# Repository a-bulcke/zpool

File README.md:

# zpool V2
Carte Zigbbe de gestion de piscine avec mesure pH, Orp, température et pression

### ATTENTION ERREUR R26=0 ohm

**Les nouveautés :** 

    Filtre sur l'alimentation USB du Xiao

    Régulation LDO coté capteurs pour enlever les bruits provenant du Xiao et de l'ADM3260.

    Alimentation AOP et ADS1115 en 4.7V

    Utilisation d'une référence de tension 2.35V (4.7/2) au lieu des ponts diviseurs non bufferisés

    Gain Orp passe de 2.32 à 2

    Guard ring pour éviter les courants de fuite au niveau des sondes (dont l'impédance est très élevé ce qui peut expliquer l'éventuelle dérive sur la v1.0)

    Connecteur I2C en 3.3V pour écran Oled ou autre

**Sources :** 

https://github.com/Loic74650/pH_Orp_Board

https://www.360customs.de/fr/2019/12/orp-redox-ph-elektrometer-shield-fuer-wemos-d1-mini-mit-lmp7721-ads1115-adm3260/

https://www.ti.com/lit/ds/symlink/lmp7721.pdf?ts=1769807145680&ref_url=https%253A%252F%252Fwww.ti.com%252Fproduct%252FLMP7721

## Xiao ESP32C6
Utilisation d'un ESP32C6 pour en faire un routeur Zigbee.

Fonctionne avec Zigbee2Mqtt sous Home Assistant.

La carte mesure le pH, l’ Orp, la température et la pression.

La gestion des pompes est assurée par des prises Zigbee c’est plus simple que d’ajouter des relais à la carte.

# Branchements #
## température et pression ##

## pH et Orp ##

# Zigbee2Mqtt #
Dans Zigbee2mqtt sous Home Assistant, laller dans le menu `Paramètres` puis `console de developpement - convertisseurs externes` :

Créer un nouveau convertisseur (de nom ZPool.js) et coller le contenu de [ZPool.js](https://github.com/a-bulcke/zpool/blob/main/zigbee2mqtt/ZPool.js)

Redémarrer Zigbee2mqtt puis autoriser l'association.

# Mise à jour

## Programmation - Mise à jour

Dans Arduino IDE

Dans File - Preferences... ajouter :

```https://espressif.github.io/arduino-esp32/package_esp32_index.json```

Choisir une carte XIAO_ESP32C6 :

Dans Tools choisir Partition scheme: "Zigbee ZCZR 4MB with spiffs" et Zigbee Mode: "ZCZR (coordinator/router)"

Et copier coller le code dans Arduino IDE :

Mettre ```Erase All Flash before sketch Upload : Disabled``` pour conserver l'appairage zigbee

Installer les bibliothèques : 
Chercher et installer : 
```
#include "OneWireESP32.h" //esp32-ds18b20 par junkfix
#include <ADS1X15.h> //ADS1X15 par Rob Tillaart
#include "RunningAverage.h" // RunningAverage par Rob Tillaart
```

Puis Upload :

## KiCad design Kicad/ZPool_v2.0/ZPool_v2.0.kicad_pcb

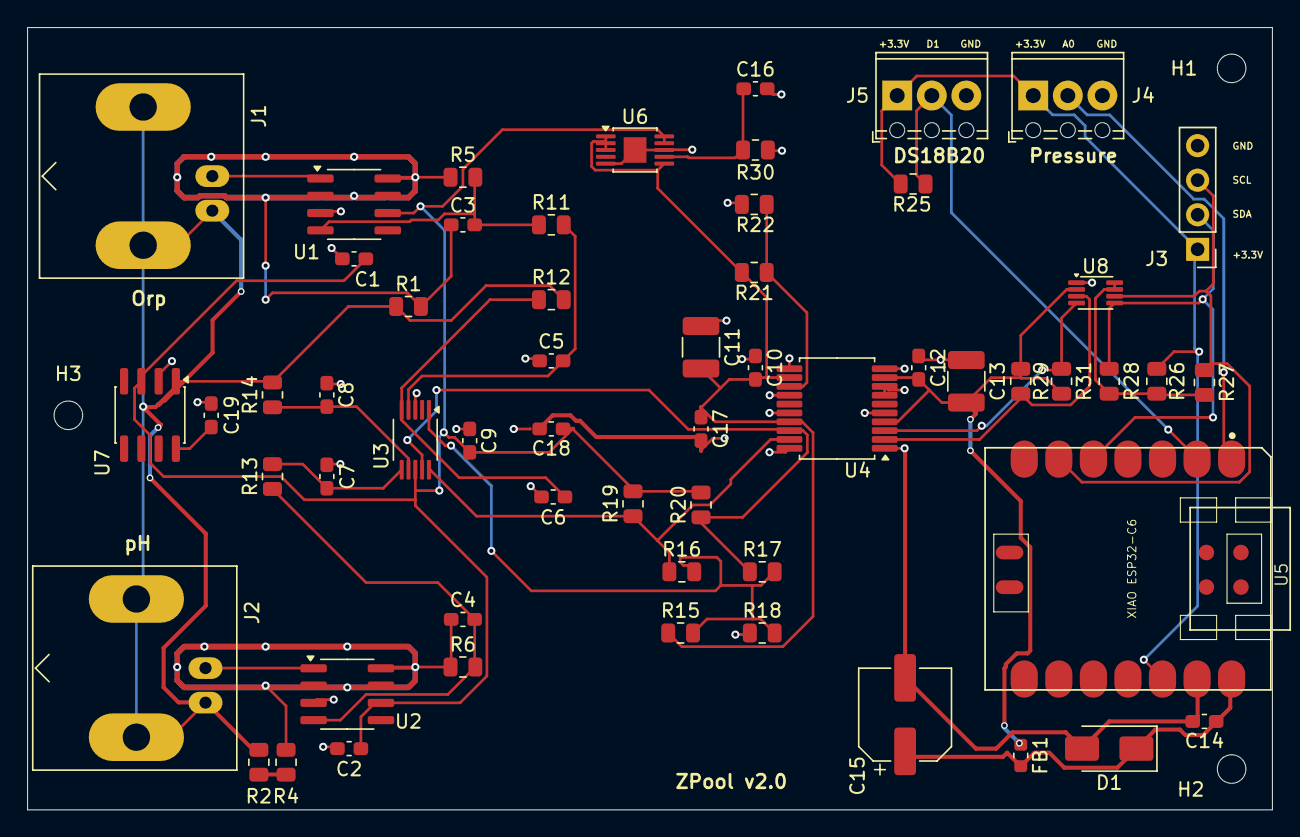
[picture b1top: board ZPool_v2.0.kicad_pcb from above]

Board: 2 copper layers, 91.5 x 57.5 mm, 61 parts (0 on the bottom side), 30 nets.

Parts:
C1, C2, C3, C4, C9, C10, C12: 100nF; C_0603_1608Metric_Pad1.08x0.95mm_HandSolder
C5, C6, C7, C8: 1uF; C_0603_1608Metric_Pad1.08x0.95mm_HandSolder
C11, C13: 10uF; C_1210_3225Metric_Pad1.33x2.70mm_HandSolder
C14: 100n; C_0603_1608Metric_Pad1.08x0.95mm_HandSolder
C15: 470u; CP_Elec_6.3x5.7
C16: 10nF; C_0603_1608Metric_Pad1.08x0.95mm_HandSolder
C17, C18: 4.7uF; C_0603_1608Metric_Pad1.08x0.95mm_HandSolder
C19: 1nF; C_0603_1608Metric_Pad1.08x0.95mm_HandSolder
D1: SMAJ5.0A; D_SMA
FB1: FerriteBead; L_0603_1608Metric
H1, H2, H3: MountingHole; MountingHole_2.1mm
J1, J2: Conn_Coaxial; BNC_Amphenol_B6252HB-NPP3G-50_Horizontal
J3: Conn_01x04_Male; PinHeader_1x04_P2.54mm_Vertical
J4: Conn_Pression; TerminalBlock_Phoenix_MPT-0,5-3-2.54_1x03_P2.54mm_Horizontal
J5: Conn_DS18B20; TerminalBlock_Phoenix_MPT-0,5-3-2.54_1x03_P2.54mm_Horizontal
R1, R5: 150K; R_0805_2012Metric
R2: 100K; R_0805_2012Metric
R4: 51K; R_0805_2012Metric
R6: 1M; R_0805_2012Metric
R11, R12, R13, R14: 10K; R_0805_2012Metric
R15, R16, R17, R18: 0; R_0805_2012Metric
R19, R20, R25, R27, R28, R29, R31: 4K7; R_0805_2012Metric
R21: R30.9K; R_0805_2012Metric
R22: R10K; R_0805_2012Metric
R26: 200K; R_0805_2012Metric
R30: 47K; R_0805_2012Metric
U1, U2: LMP7721MA/NOPB; SOIC-8_3.9x4.9mm_P1.27mm
U3: ADS1115IDGS; VSSOP-10_3x3mm_P0.5mm
U4: ADM3260; SSOP-20_5.3x7.2mm_P0.65mm
U5: XIAO ESP32-C6; Seeeduino XIAO-MOUDLE14P-2.54-21X17.8MM
U6: LT3042xMSE; MSOP-10-1EP_3x3mm_P0.5mm_EP1.68x1.88mm
U7: TLE2426xD; SOIC-8_3.9x4.9mm_P1.27mm
U8: PCA9306; VSSOP-8_2.3x2mm_P0.5mm

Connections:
+2.35V Iso: J1.2 (Ext), J2.2 (Ext), R1.1, R2.1, R12.2, R14.2, U7.1 (OUT)
+3.3V: J3.1, J4.1, J5.1, R25.1, R26.2, U5.12 (3V3)
+4.7V Iso: C1.2, C2.2, C9.2, C18.1, R19.2, R20.2, U1.6, U2.6, U3.8 (VDD), U6.9 (OUTS), U6.10 (OUT), U7.3 (IN)
+5V: C12.2, C13.2, FB1.1, R29.2, R31.2, U4.4 (VDDP), U4.9 (VIN), U8.2 (VREF1)
+5V Iso: C10.2, C11.2, C17.1, R15.1, R21.1, U4.12 (VISO), U4.17 (VDDISO), U6.1 (IN), U6.2 (IN), U6.3 (EN/UV), U6.6 (PGFB)
+5V_XIAO: C14.1, C15.1, D1.1 (A1), FB1.2, U5.14 (5V)
A0: J4.2, U5.1 (PA02_A0_D0)
D1: J5.2, R25.2, U5.2 (PA4_A1_D1)
GND: C12.1, C13.1, C14.2, C15.2, D1.2 (A2), J3.4, J4.3, J5.3, U4.1 (GNDP@1), U4.5 (GNDP@2), U4.7 (GNDP@2), U4.8 (PDIS), U4.10 (GNDP@2), U5.13 (GND), U8.1 (GND)
GND Iso: C1.1, C2.1, C5.1, C6.1, C7.1, C8.1, C9.1, C10.1, C11.1, C16.2, C17.2, C18.2, C19.2, R18.1, R22.1, R30.1, U1.3, U2.3, U3.3 (GND), U4.11 (GNDISO@2), U4.14 (GNDISO@2), U4.16 (GNDISO@2), U4.20 (GNDISO@1), U6.5 (ILIM), U6.8 (GND), U6.11 (GND), U7.2 (COMMON)
unnamed: C3.2, R5.2, R11.1, U1.4
unnamed: C4.2, R6.2, R13.1, U2.4
unnamed: J1.1 (In), U1.1
unnamed: J2.1 (In), U2.1
unnamed: R2.2, R4.1
unnamed: R15.2, R16.2, R17.2, R18.2, U3.1 (ADDR)
unnamed: C5.2, R11.2, U3.4 (AIN0)
unnamed: C6.2, R12.1, U3.5 (AIN1)
unnamed: C7.2, R13.2, U3.6 (AIN2)
unnamed: C8.2, R14.1, U3.7 (AIN3)
unnamed: R16.1, R19.1, U3.10 (SCL), U4.19 (SCL1)
unnamed: R17.1, R20.1, U3.9 (SDA), U4.18 (SDA1)
unnamed: R21.2, R22.2, U4.13 (VSEL)
unnamed: C16.1, R30.2, U6.7 (SET)
unnamed: C19.1, U7.8 (NOISE_REDUCTION)
unnamed: R26.1, R27.2, R28.2, U8.7 (VREF2), U8.8 (EN)
SCL: R29.1, U4.2 (SCL2), U8.3 (SCL1)
SCL3.3: J3.3, R27.1, U5.6 (PA9_A5_D5_SCL), U8.6 (SCL2)
SDA: R31.1, U4.3 (SDA2), U8.4 (SDA1)
SDA3.3: J3.2, R28.1, U5.5 (PA8_A4_D4_SDA), U8.5 (SDA2)

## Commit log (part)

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2026-01-30 v1.0
2026-01-30 Update README with sources and images
    Added source links and images to README.
2026-01-30 Add image of Boitier to README
2026-01-31 Add temperature and pressure sensor images to README
2026-01-31 Enhance README for ESP32C6 Zigbee router
    Updated the description of the ESP32C6 usage and added functionality details. Included images with specified widths.
2026-02-05 Add carte_xiao image to README
    Added image of carte_xiao to the README.
2026-02-05 Add Zigbee module image to README
    Added an image of the Zigbee module to the README.
2026-02-06 Add additional image to README
2026-02-06 Replace zpoolv1.png with zpoolv1.jpg in README
2026-02-14 Update README with Arduino IDE configuration details
    Added Arduino IDE setup instructions for XIAO_ESP32C6.
2026-02-14 Update README with new connection sections
    Added sections for temperature, pressure, pH, and Zigbee2Mqtt.
2026-02-14 Update README with converter creation instructions
    Updated instructions for creating a new converter in Zigbee2mqtt, including a link to the ZigbeePoolSensorsCalib.js file.
2026-02-14 Update README with additional instructions for Zigbee2mqtt
2026-03-18 Fix image link format for DS18B20 sensor
    Updated the image link format for temperature sensor.
2026-03-18 Fix image link for DS18B20 temperature sensor
    Updated the image link for the DS18B20 temperature sensor in the README.
2026-03-18 Change temperature sensor image URL
    Updated image link for temperature sensor in README.
2026-03-18 Fix image URLs in README
    Updated image URLs for temperature and pressure sensors.
2026-03-28 Change pH reporting change threshold to 0.05
2026-03-28 Add Zigbee temperature and pressure sensor code
2026-03-29 Update version to 1.11 and add external antenna config
2026-03-29 Add initial configuration for pool sensors
2026-03-29 Configure WIFI_ENABLE pin for external antenna
2026-03-29 Update README with sensor images and links
    Added images and links for temperature and pressure sensors.
2026-03-31 Update README with Arduino IDE programming instructions
    Added instructions for programming with Arduino IDE and configuring Zigbee settings.
2026-03-31 Improve code snippet formatting in README
    Updated formatting for URLs and code snippets in the README.
2026-03-31 Revise programming instructions and add images
    Updated programming section with new instructions and images.
2026-03-31 Update project version from V1.0 to V1
2026-04-11 Update version to 1.12 and adjust ORP reading
2026-05-24 Fix comment formatting for pH calculation
2026-05-30 1.3.3 pre release
    Version préliminaire avec choix des solutions d'étalonnage, 3 points d'étalonnage pour le pH, OTA, et filtre de Kalman.
2026-05-30 Update README with image and sources
    Added an image and updated sources section.
2026-05-30 Adjust image dimensions in README.md
    Updated image size in README for better display.
2026-05-30 Include image in README.md
    Add image to README for zpool V1 project
2026-05-30 Upgrade ZPool.js to version 1.3.5
    Updated ZPool.js to version 1.3.5 with new measurements and calibration triggers.
2026-05-30 Bump version to 1.3.5 and update changelog
    Updated version to 1.3.5 with calibration timing adjustments and thermal correction using Nernst equation.
2026-05-31 Pre release 1.3.5
2026-05-31 pre release 1.5
2026-05-31 v1.1
2026-06-02 Change gain setting and update ADC read functions
2026-06-02 Change ADS gain and update ADC readings
2026-06-02 Change ADC gain and update differential readings
2026-06-02 Swap multiplexer channels for ADS1115 sensors
2026-06-02 Update ORP voltage calibration formula
    Adjust calibration calculation for ORP voltage.
2026-06-03 Fix ADS1115 channel assignments in zpool_v1_0.yaml
    Updated ADS1115 channel assignments for pH and ORP sensors.
2026-06-03 Fix ADS1115 multiplexer channels for pH and ORP
2026-06-20 Update README with new image and instructions
    Added a new image and updated instructions in the README.
2026-06-22 Remove 1.3.3 & 1.3.2 versions in ZPool.js 1.3.5
    Removed the ZPool device configuration and related measurements.
